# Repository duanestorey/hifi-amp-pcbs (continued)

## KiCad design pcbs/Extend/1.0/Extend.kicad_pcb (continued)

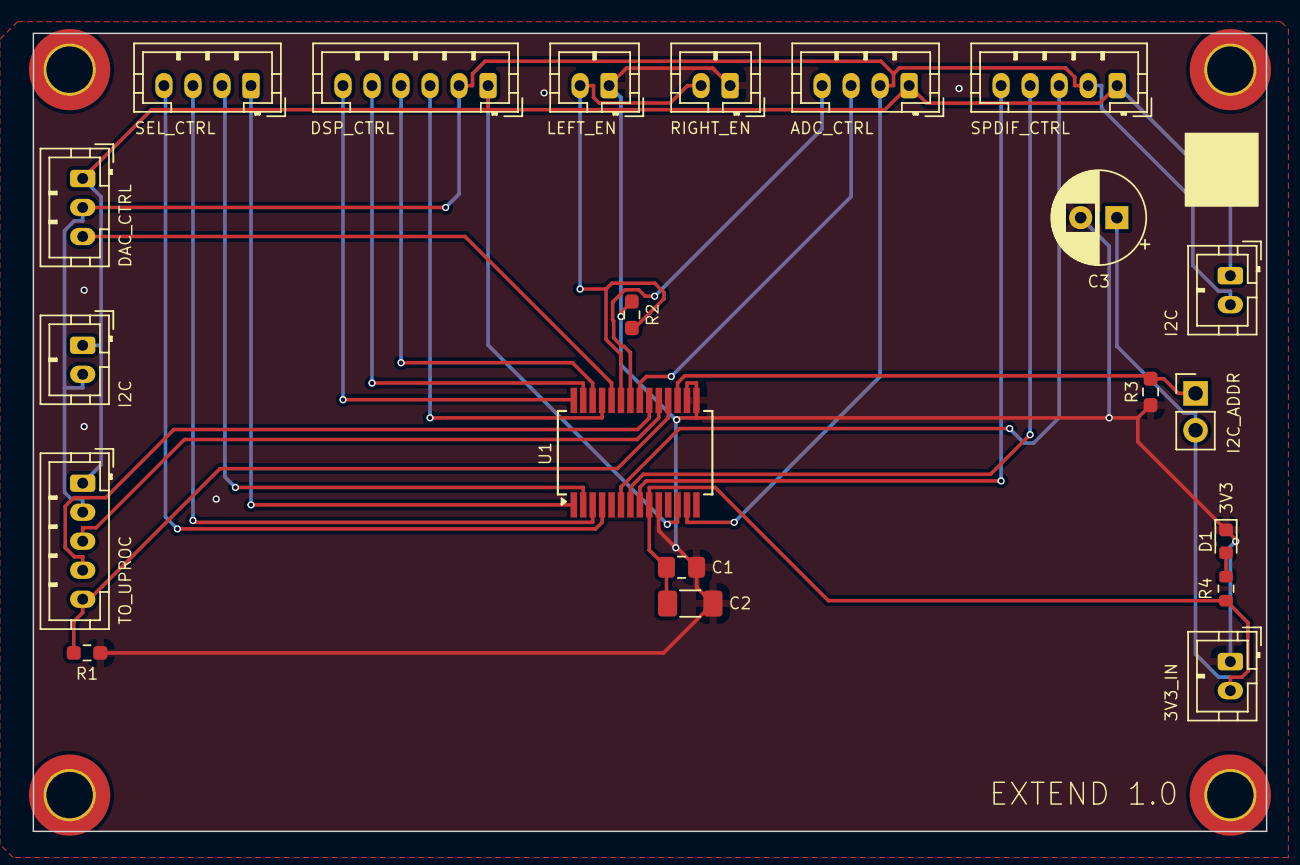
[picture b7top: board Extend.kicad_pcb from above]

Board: 2 copper layers, 85.0 x 55.0 mm, 25 parts (0 on the bottom side), 24 nets.

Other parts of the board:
J12: Conn_01x03_Pin; JST_PH_B3B-PH-K_1x03_P2.00mm_Vertical

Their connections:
DAC_XSMT: J12.3; also elsewhere on the board
SCL: J12.1; also elsewhere on the board
SDA: J12.2; also elsewhere on the board

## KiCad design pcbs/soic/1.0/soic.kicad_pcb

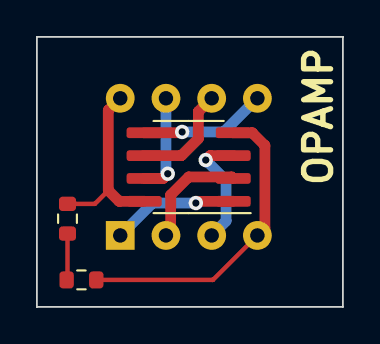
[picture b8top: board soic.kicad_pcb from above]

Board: 2 copper layers, 17.0 x 15.0 mm, 4 parts (0 on the bottom side), 9 nets.

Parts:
D1: LED; R_0603_1608Metric
R1: 10K; R_0603_1608Metric
U1: OPA2134; DIP-8_W7.62mm_Socket
U2: OPA2134; SOIC-8_3.9x4.9mm_P1.27mm

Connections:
1: U1.1 (OutA), U2.1 (OutA)
2: U1.2 (InA-), U2.2 (InA-)
3: U1.3 (InA+), U2.3 (InA+)
4: D1.1 (K), U1.4 (V-), U2.4 (V-)
5: U1.5 (InB+), U2.5 (InB+)
6: U1.6 (InB-), U2.6 (InB-)
7: U1.7 (OutB), U2.7 (OutB)
8: R1.1, U1.8 (V+), U2.8 (V+)
unnamed: D1.2 (A), R1.2

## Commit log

2025-01-04 Updates to PCBs
2025-01-04 Moving PCBs
2025-01-04 updating names
2025-01-04 Updating PCBs
2025-01-04 Updated screenshots
2025-01-04 Updating readmes
2025-01-04 Renamed
2025-01-05 Updating readme files
2025-01-05 test
2025-01-12 More work on PCBs
